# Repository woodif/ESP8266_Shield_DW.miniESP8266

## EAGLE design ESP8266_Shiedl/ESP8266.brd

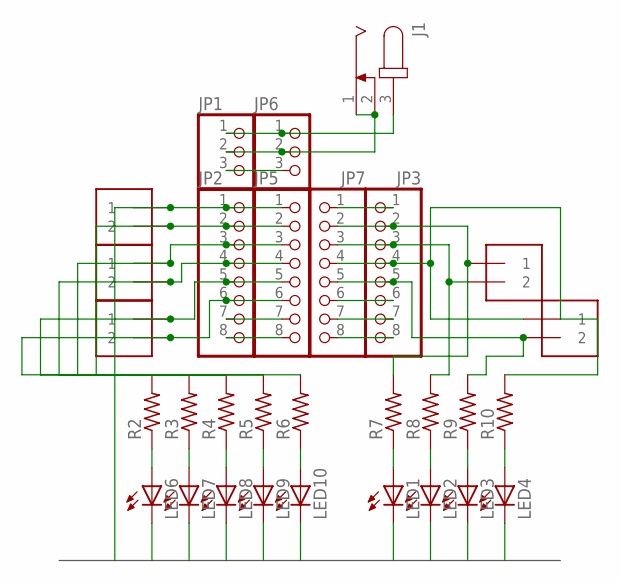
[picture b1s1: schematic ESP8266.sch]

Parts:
J1: JACK-PLUG0; SPC4077
J2, J3, J4, J7, J8: 1X2-3.5MM
JP1, JP6: PINHD-1X3; 1X03
JP2, JP3, JP5, JP7: PINHD-1X8BIG; 1X08-BIG
LED1, LED2, LED3, LED4, LED6, LED7, LED8, LED9, LED10: LEDCHIP-LED0805; CHIP-LED0805
R2, R3, R4, R5, R6, R7, R8, R9, R10: R-US_R0805; R0805

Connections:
GND: J1.1, J1.2, J2.1, JP1.2, JP2.1, JP5.1, JP6.2, LED1.C, LED2.C, LED3.C, LED4.C, LED6.C, LED7.C, LED8.C, LED9.C, LED10.C
unnamed: J7.1, JP3.2, JP7.2, R7.2
unnamed: J8.1, JP3.4, JP7.4, R10.2
unnamed: J7.2, JP3.3, JP7.3, R8.2
unnamed: J2.2, JP2.2, JP5.2, R2.2
unnamed: J3.1, JP2.3, JP5.3, R3.2
unnamed: J3.2, JP2.4, JP5.4, R4.2
unnamed: J4.1, JP2.5, JP5.5, R5.2
unnamed: J4.2, JP2.6, JP5.6, R6.2
unnamed: J1.3, JP1.1, JP6.1
unnamed: JP1.3, JP6.3
unnamed: JP2.7, JP5.7
unnamed: JP2.8, JP5.8
unnamed: JP3.1, JP7.1
unnamed: JP3.6, JP7.6
unnamed: JP3.7, JP7.7
unnamed: JP3.8, JP7.8
unnamed: J8.2, JP3.5, JP7.5, R9.2
unnamed: LED6.A, R2.1
unnamed: LED7.A, R3.1
unnamed: LED8.A, R4.1
unnamed: LED9.A, R5.1
unnamed: LED10.A, R6.1
unnamed: LED1.A, R7.1
unnamed: LED2.A, R8.1
unnamed: LED3.A, R9.1
unnamed: LED4.A, R10.1

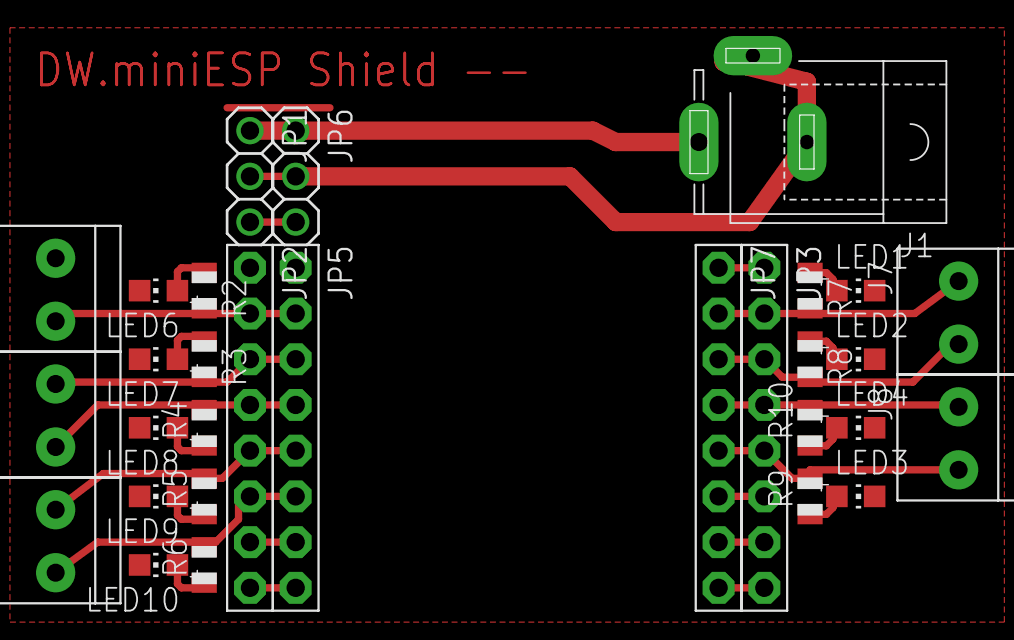
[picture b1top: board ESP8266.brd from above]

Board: 2 copper layers, 30 parts (0 on the bottom side), 27 nets.

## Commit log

2015-07-28 frist commit
